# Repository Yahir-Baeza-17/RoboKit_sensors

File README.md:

# RoboKit_sensors
El  siguiente apartado presenta el espacio de trabajo donde se encuentra el nodo de lectura de los sensores, incluyendo el código de Arduino de los mismos

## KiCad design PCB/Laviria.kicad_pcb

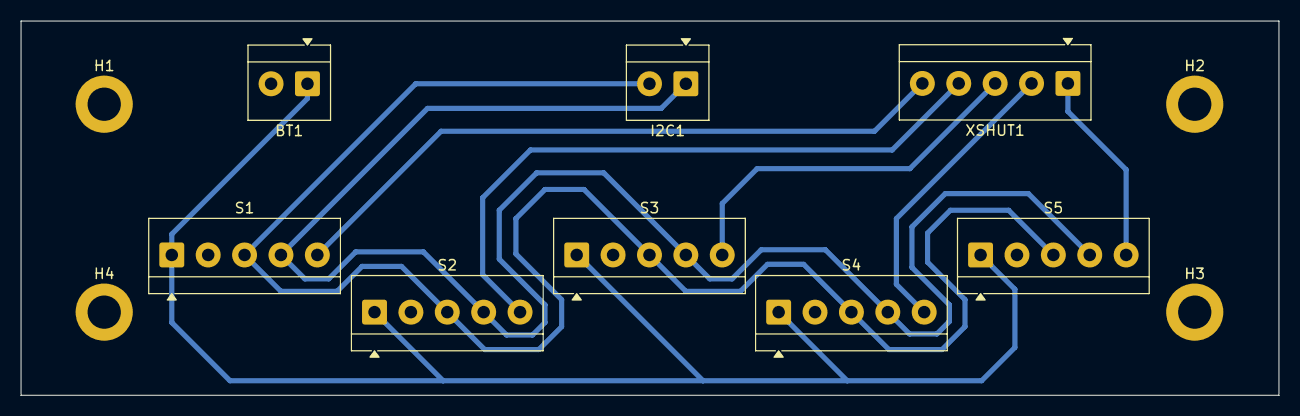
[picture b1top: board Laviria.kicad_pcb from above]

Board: 2 copper layers, 121.0 x 36.0 mm, 12 parts (0 on the bottom side), 9 nets.

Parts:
BT1: Battery; TerminalBlock_4Ucon_1x02_P3.50mm_Horizontal
H1, H2, H3, H4: MountingHole_3.2mm_M3_ISO14580_Pad
I2C1: Screw_Terminal_01x02; TerminalBlock_4Ucon_1x02_P3.50mm_Horizontal
S1, S2, S3, S4, S5: Screw_Terminal_01x05; TerminalBlock_4Ucon_1x05_P3.50mm_Horizontal
XSHUT1: Screw_Terminal_01x05; TerminalBlock_4Ucon_1x05_P3.50mm_Horizontal

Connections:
GND: BT1.2 (-), H1.1, H2.1, H3.1, H4.1, S1.2, S2.2, S3.2, S4.2, S5.2
SCL: I2C1.1, S1.4, S2.4, S3.4, S4.4, S5.4
SDA: I2C1.2, S1.3, S2.3, S3.3, S4.3, S5.3
Vcc: BT1.1 (+), S1.1, S2.1, S3.1, S4.1, S5.1
XSHUT1: S1.5, XSHUT1.5
XSHUT2: S2.5, XSHUT1.4
XSHUT3: S3.5, XSHUT1.3
XSHUT4: S4.5, XSHUT1.2
XSHUT5: S5.5, XSHUT1.1

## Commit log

2026-04-22 Estructura inicial del workspace y nodo de sensores VL53L0X
